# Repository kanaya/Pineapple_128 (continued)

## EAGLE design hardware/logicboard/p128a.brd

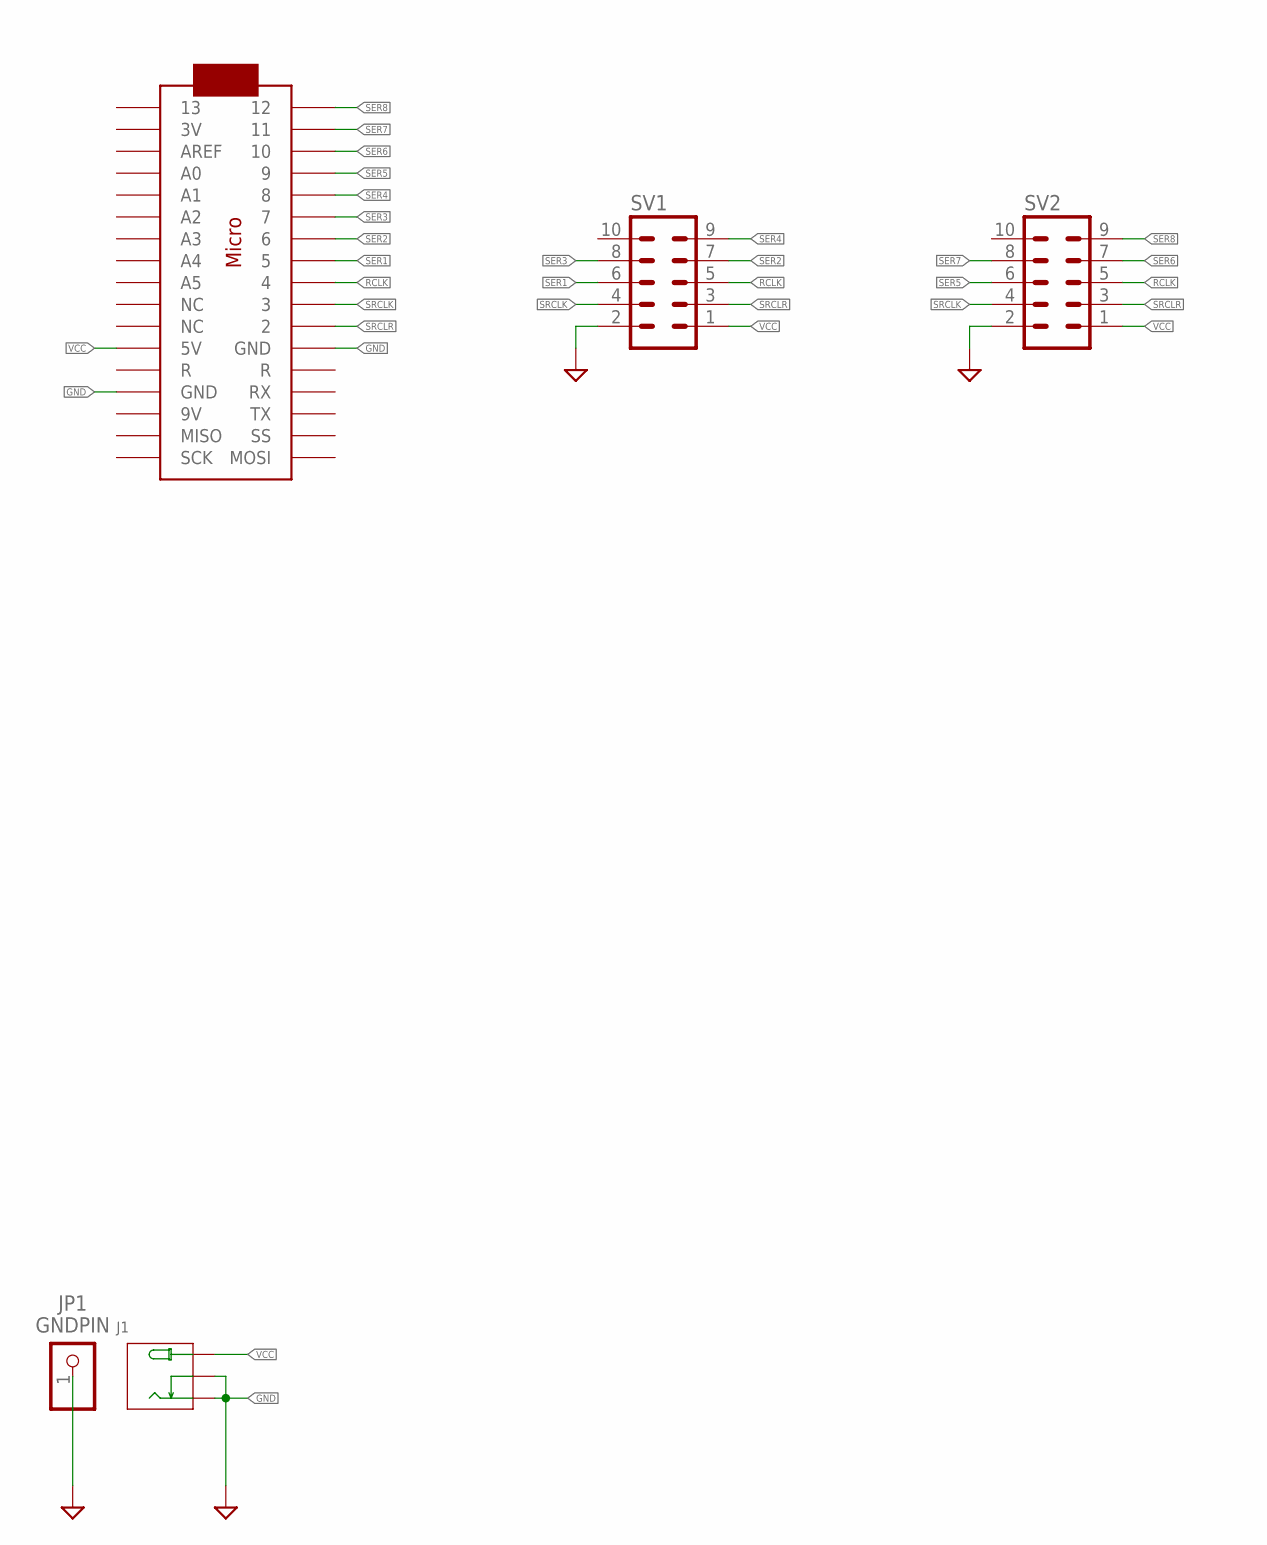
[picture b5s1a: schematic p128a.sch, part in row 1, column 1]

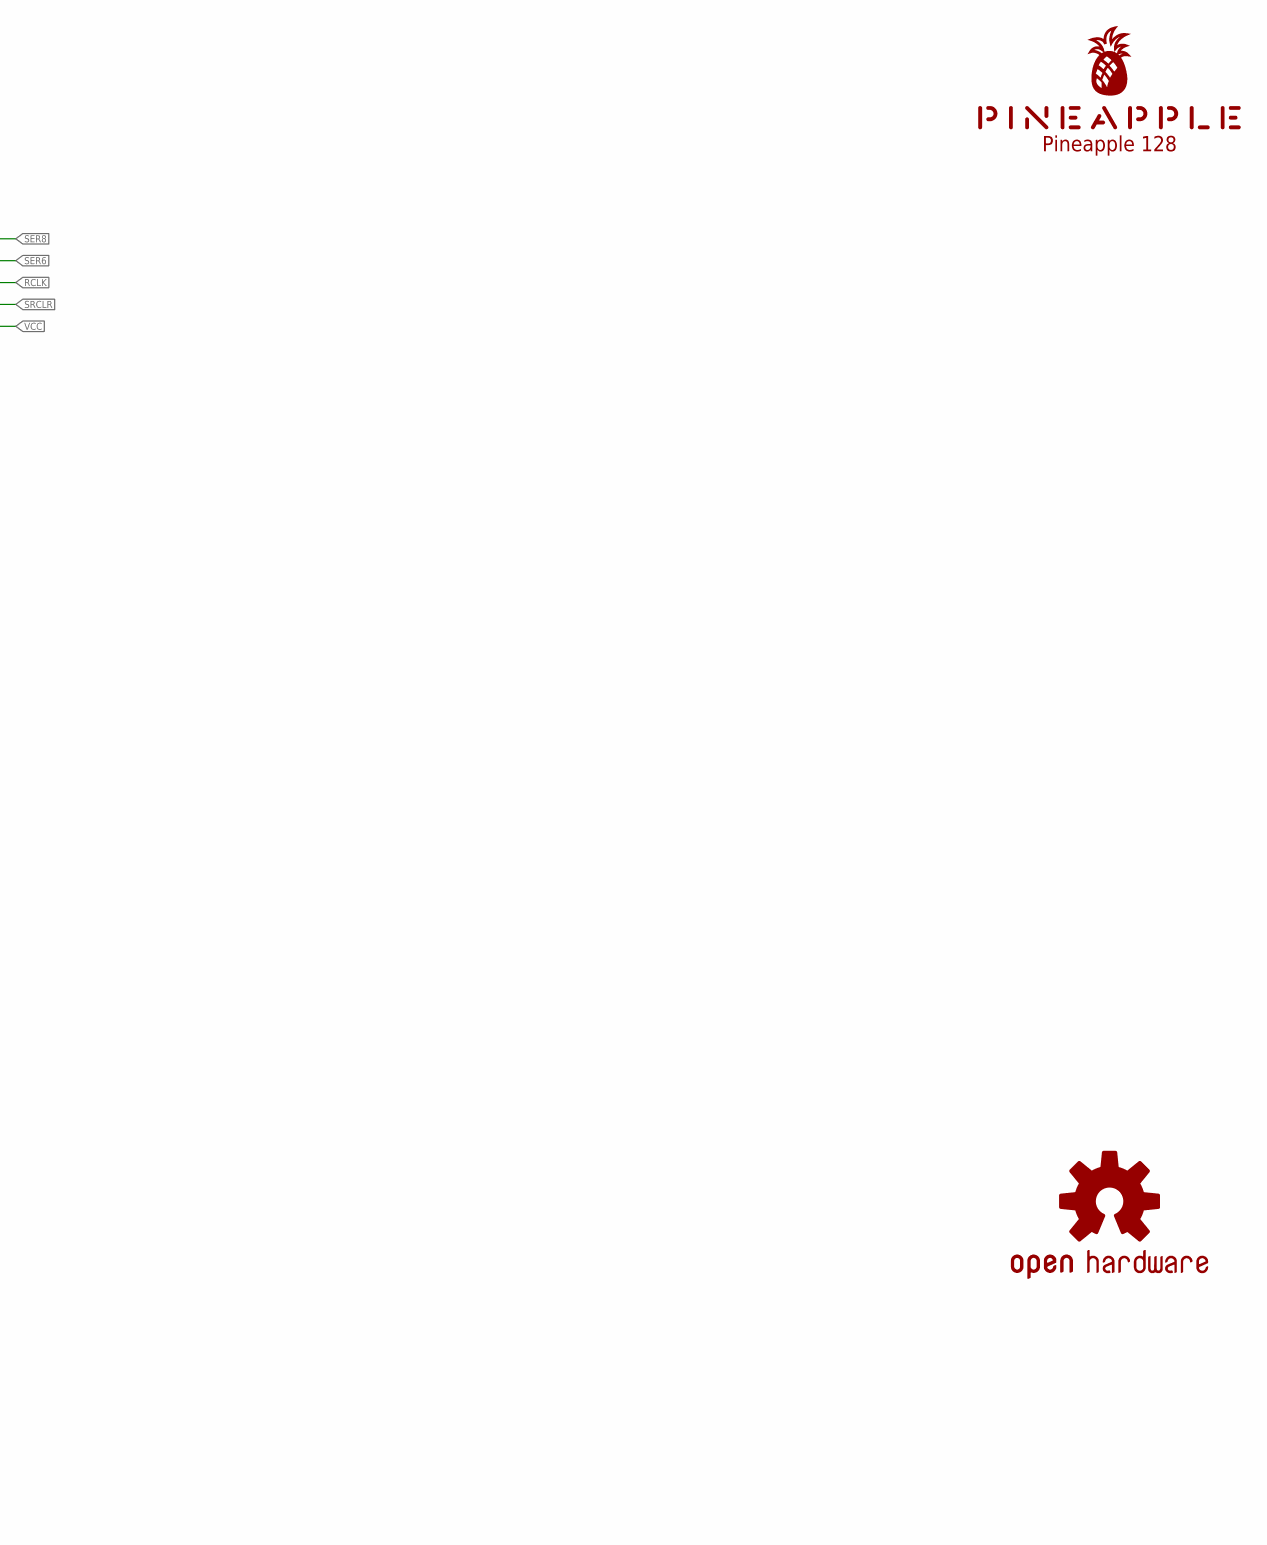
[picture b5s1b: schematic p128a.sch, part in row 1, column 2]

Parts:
J1: JACK-DC-005'DC-005'; 3P-L14.2*W11.0*H9.0MM
JP1: GNDPIN; 1X01
LOGO1: OSHW-LOGOS-COPPER; OSHW-LOGO-S_COPPER
MC1: ARDUINOMICRO
SV1, SV2: ML10L
U$1: PINEAPPLE450_SILK

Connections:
GND: J1.-1 (-), J1.-2 (CDN), JP1.1, MC1.P$12 (GND), MC1.P$21 (GND), SV1.2, SV2.2
RCLK: MC1.P$9 (4), SV1.5, SV2.5
SER1: MC1.P$8 (5), SV1.6
SER2: MC1.P$7 (6), SV1.7
SER3: MC1.P$6 (7), SV1.8
SER4: MC1.P$5 (8), SV1.9
SER5: MC1.P$4 (9), SV2.6
SER6: MC1.P$3 (10), SV2.7
SER7: MC1.P$2 (11), SV2.8
SER8: MC1.P$1 (12), SV2.9
SRCLK: MC1.P$10 (3), SV1.4, SV2.4
SRCLR: MC1.P$11 (2), SV1.3, SV2.3
VCC: J1.+, MC1.P$23 (5V), SV1.1, SV2.1

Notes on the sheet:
Pineapple 128

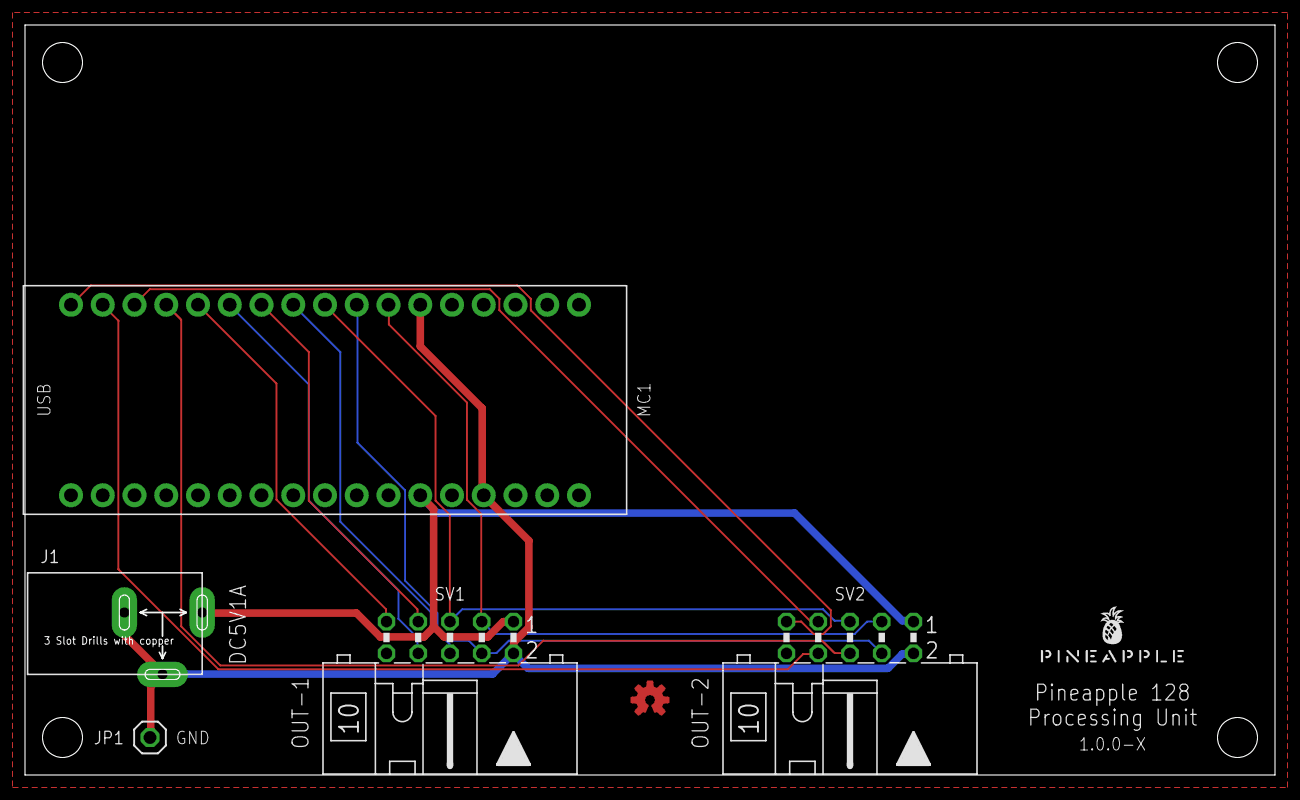
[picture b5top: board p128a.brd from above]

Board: 2 copper layers, 99.9 x 59.9 mm, 7 parts (0 on the bottom side), 13 nets.

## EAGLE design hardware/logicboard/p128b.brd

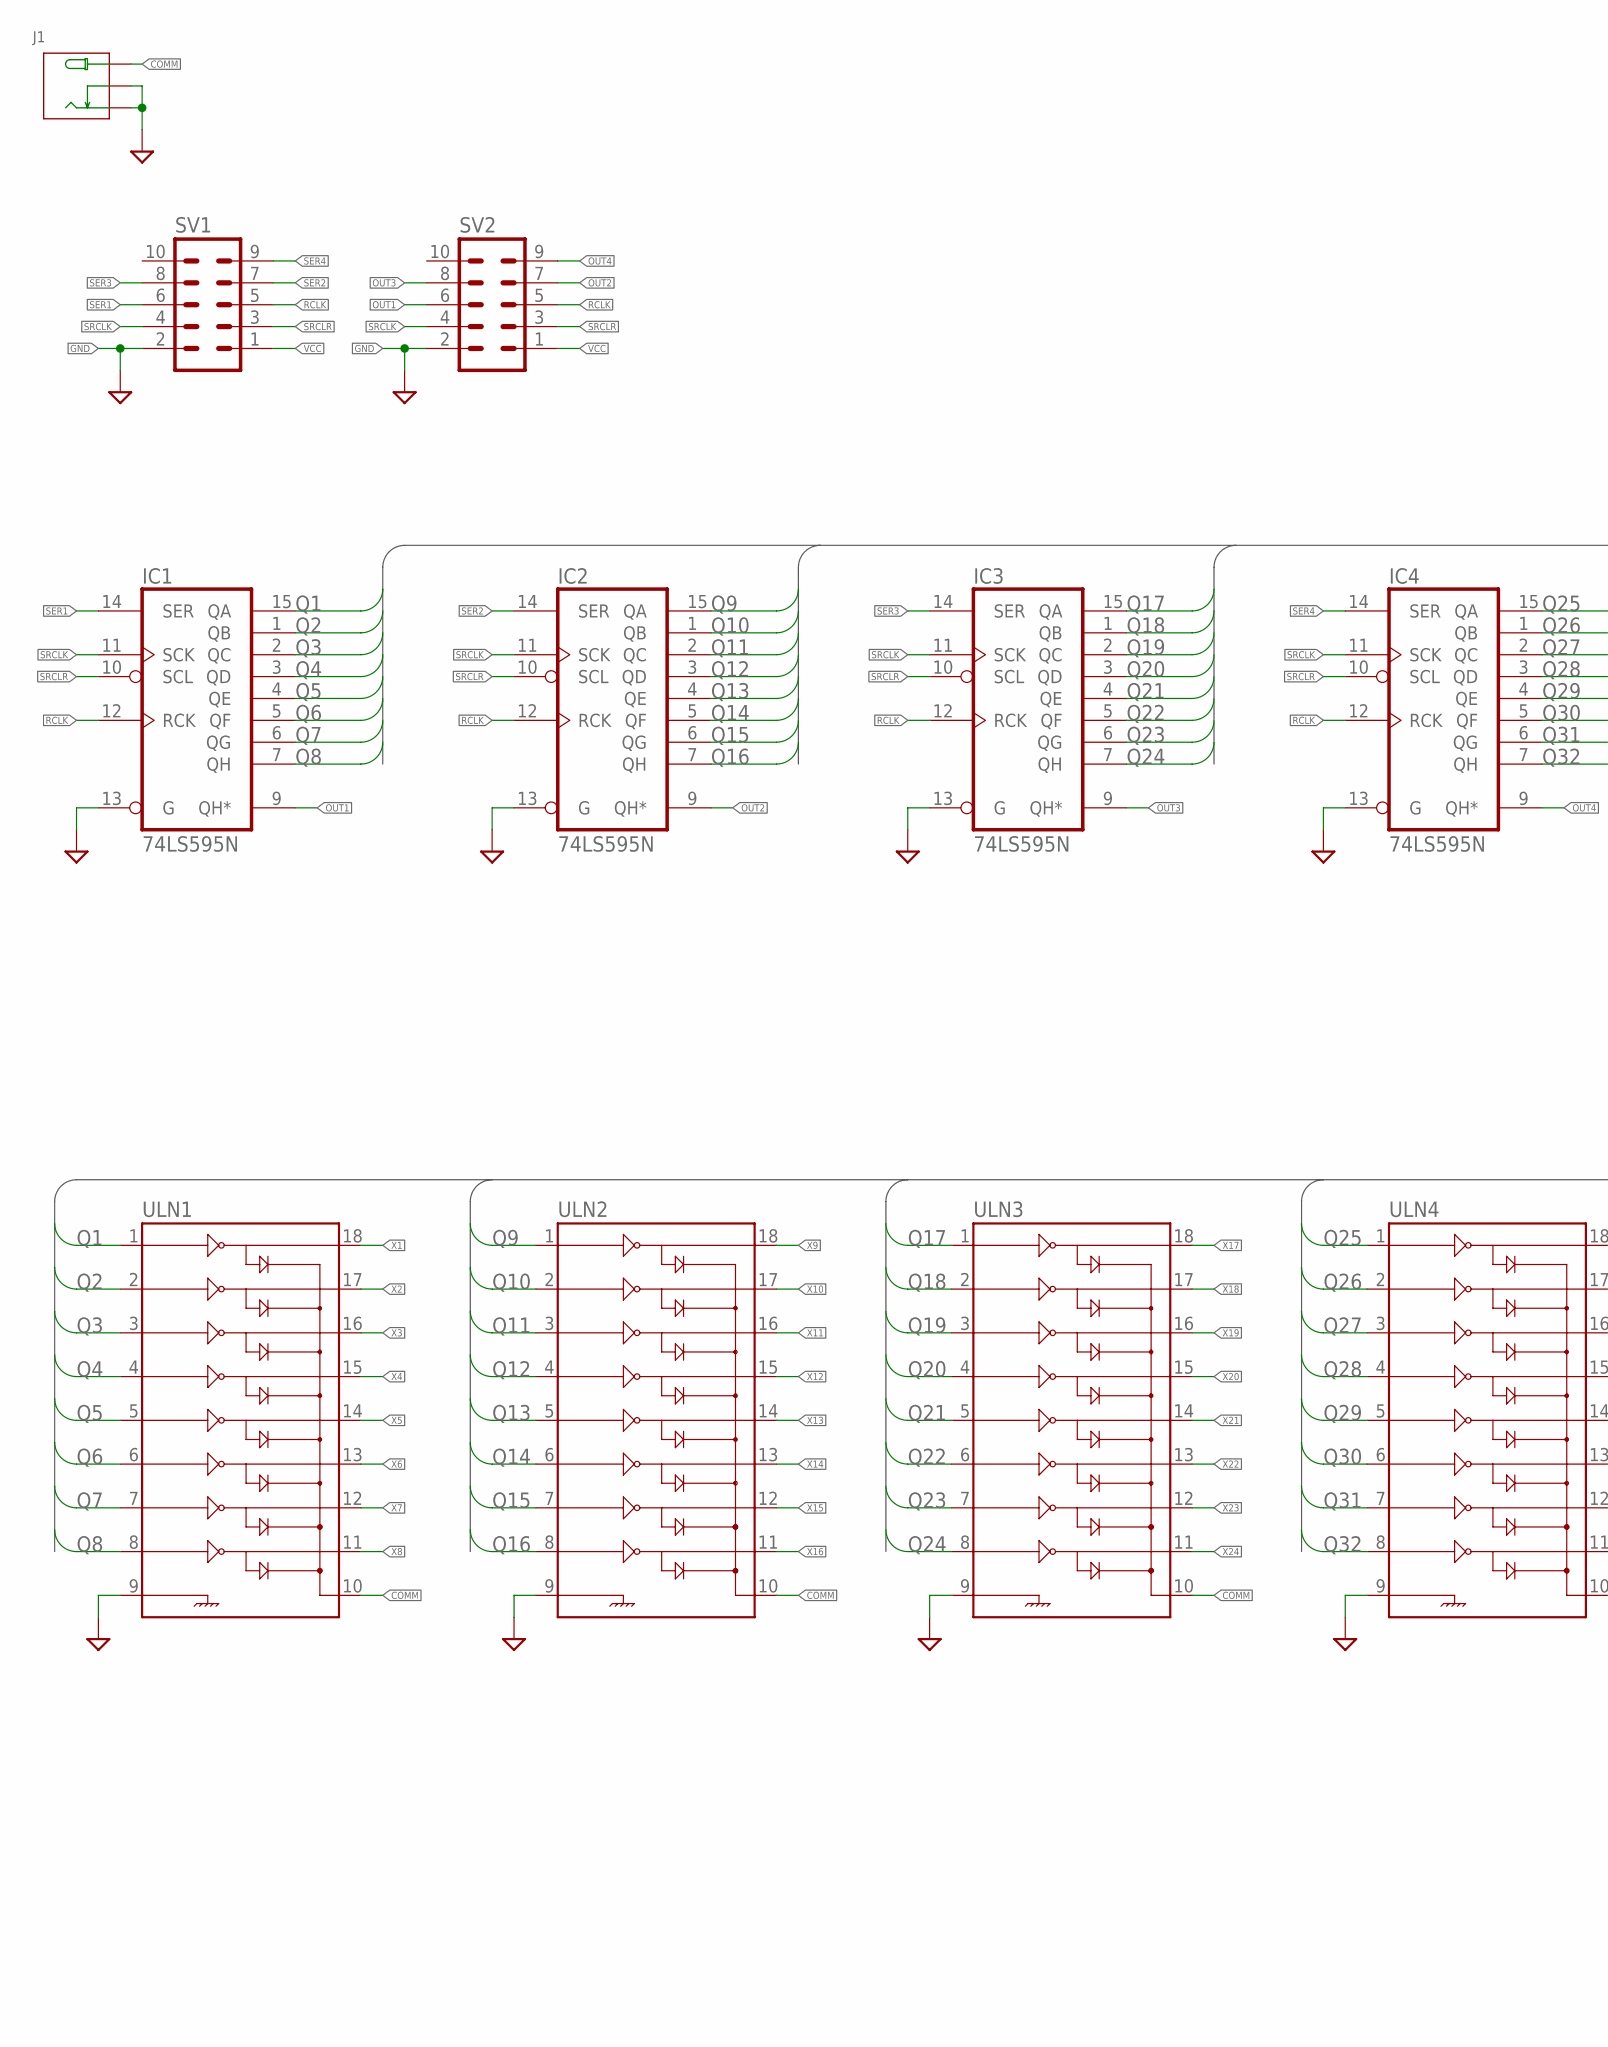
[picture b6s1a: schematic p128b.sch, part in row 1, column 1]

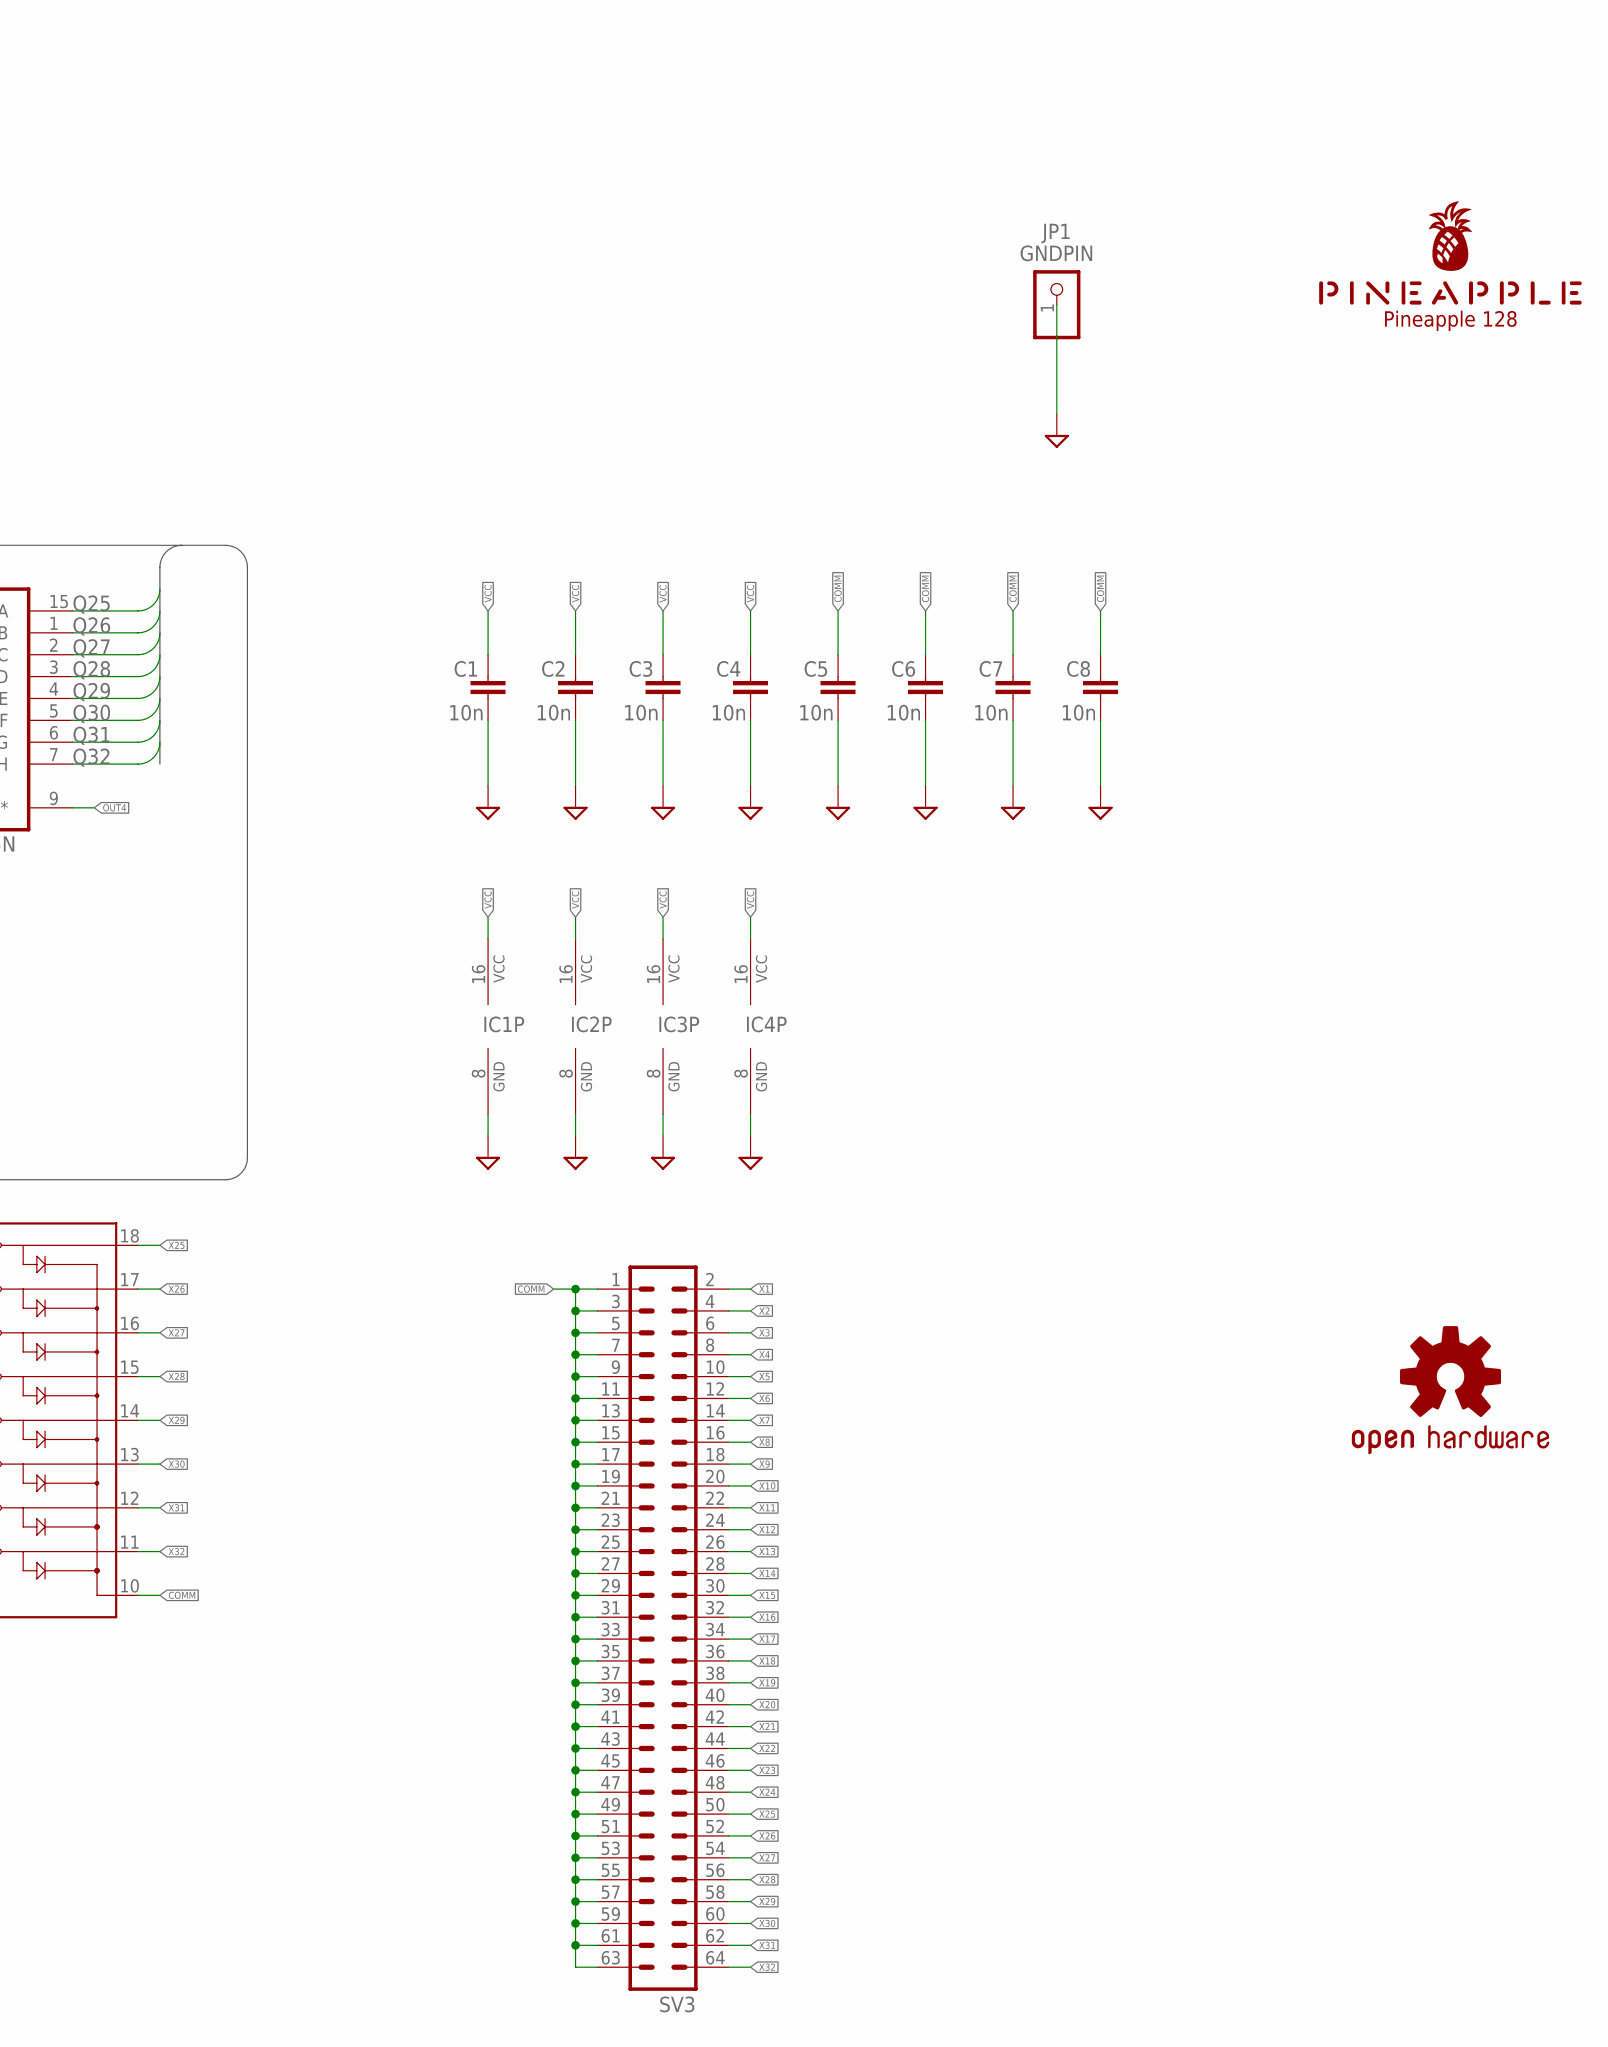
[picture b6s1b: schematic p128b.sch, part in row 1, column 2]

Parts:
C1, C2, C3, C4, C5, C6, C7, C8: 10n; C025-024X044
IC1, IC2, IC3, IC4: 74LS595N; DIL16
J1: JACK-DC-005'DC-005'; 3P-L14.2*W11.0*H9.0MM
JP1: GNDPIN; 1X01
LOGO1: OSHW-LOGOS-COPPER; OSHW-LOGO-S_COPPER
SV1, SV2: ML10L
SV3: ML64L
U$1: PINEAPPLE450_SILK
ULN1, ULN2, ULN3, ULN4: ULN2803DIP; DIL18

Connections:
COMM: C5.1, C6.1, C7.1, C8.1, J1.+, SV3.1, SV3.3, SV3.5, SV3.7, SV3.9, SV3.11, SV3.13, SV3.15, SV3.17, SV3.19, SV3.21, SV3.23, SV3.25, SV3.27, SV3.29, SV3.31, SV3.33, SV3.35, SV3.37, SV3.39, SV3.41, SV3.43, SV3.45, SV3.47, SV3.49, SV3.51, SV3.53, SV3.55, SV3.57, SV3.59, SV3.61, SV3.63, ULN1.10, ULN2.10, ULN3.10, ULN4.10
GND: C1.2, C2.2, C3.2, C4.2, C5.2, C6.2, C7.2, C8.2, IC1.8 (GND), IC1.13 (G), IC2.8 (GND), IC2.13 (G), IC3.8 (GND), IC3.13 (G), IC4.8 (GND), IC4.13 (G), J1.-1 (-), J1.-2 (CDN), JP1.1, SV1.2, SV2.2, ULN1.9, ULN2.9, ULN3.9, ULN4.9
OUT1: IC1.9 (QH*), SV2.6
OUT2: IC2.9 (QH*), SV2.7
OUT3: IC3.9 (QH*), SV2.8
OUT4: IC4.9 (QH*), SV2.9
Q1: IC1.15 (QA), ULN1.1
Q2: IC1.1 (QB), ULN1.2
Q3: IC1.2 (QC), ULN1.3
Q4: IC1.3 (QD), ULN1.4
Q5: IC1.4 (QE), ULN1.5
Q6: IC1.5 (QF), ULN1.6
Q7: IC1.6 (QG), ULN1.7
Q8: IC1.7 (QH), ULN1.8
Q9: IC2.15 (QA), ULN2.1
Q10: IC2.1 (QB), ULN2.2
Q11: IC2.2 (QC), ULN2.3
Q12: IC2.3 (QD), ULN2.4
Q13: IC2.4 (QE), ULN2.5
Q14: IC2.5 (QF), ULN2.6
Q15: IC2.6 (QG), ULN2.7
Q16: IC2.7 (QH), ULN2.8
Q17: IC3.15 (QA), ULN3.1
Q18: IC3.1 (QB), ULN3.2
Q19: IC3.2 (QC), ULN3.3
Q20: IC3.3 (QD), ULN3.4
Q21: IC3.4 (QE), ULN3.5
Q22: IC3.5 (QF), ULN3.6
Q23: IC3.6 (QG), ULN3.7
Q24: IC3.7 (QH), ULN3.8
Q25: IC4.15 (QA), ULN4.1
Q26: IC4.1 (QB), ULN4.2
Q27: IC4.2 (QC), ULN4.3
Q28: IC4.3 (QD), ULN4.4
Q29: IC4.4 (QE), ULN4.5
Q30: IC4.5 (QF), ULN4.6
Q31: IC4.6 (QG), ULN4.7
Q32: IC4.7 (QH), ULN4.8
RCLK: IC1.12 (RCK), IC2.12 (RCK), IC3.12 (RCK), IC4.12 (RCK), SV1.5, SV2.5
SER1: IC1.14 (SER), SV1.6
SER2: IC2.14 (SER), SV1.7
SER3: IC3.14 (SER), SV1.8
SER4: IC4.14 (SER), SV1.9
SRCLK: IC1.11 (SCK), IC2.11 (SCK), IC3.11 (SCK), IC4.11 (SCK), SV1.4, SV2.4
SRCLR: IC1.10 (SCL), IC2.10 (SCL), IC3.10 (SCL), IC4.10 (SCL), SV1.3, SV2.3
VCC: C1.1, C2.1, C3.1, C4.1, IC1.16 (VCC), IC2.16 (VCC), IC3.16 (VCC), IC4.16 (VCC), SV1.1, SV2.1
X1: SV3.2, ULN1.18
X2: SV3.4, ULN1.17
X3: SV3.6, ULN1.16
X4: SV3.8, ULN1.15
X5: SV3.10, ULN1.14
X6: SV3.12, ULN1.13
X7: SV3.14, ULN1.12
X8: SV3.16, ULN1.11
X9: SV3.18, ULN2.18
X10: SV3.20, ULN2.17
X11: SV3.22, ULN2.16
X12: SV3.24, ULN2.15
X13: SV3.26, ULN2.14
X14: SV3.28, ULN2.13
X15: SV3.30, ULN2.12
X16: SV3.32, ULN2.11
X17: SV3.34, ULN3.18
X18: SV3.36, ULN3.17
X19: SV3.38, ULN3.16
X20: SV3.40, ULN3.15
X21: SV3.42, ULN3.14
X22: SV3.44, ULN3.13
X23: SV3.46, ULN3.12
X24: SV3.48, ULN3.11
X25: SV3.50, ULN4.18
X26: SV3.52, ULN4.17
X27: SV3.54, ULN4.16
X28: SV3.56, ULN4.15
X29: SV3.58, ULN4.14
X30: SV3.60, ULN4.13
X31: SV3.62, ULN4.12
X32: SV3.64, ULN4.11

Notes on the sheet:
Pineapple 128

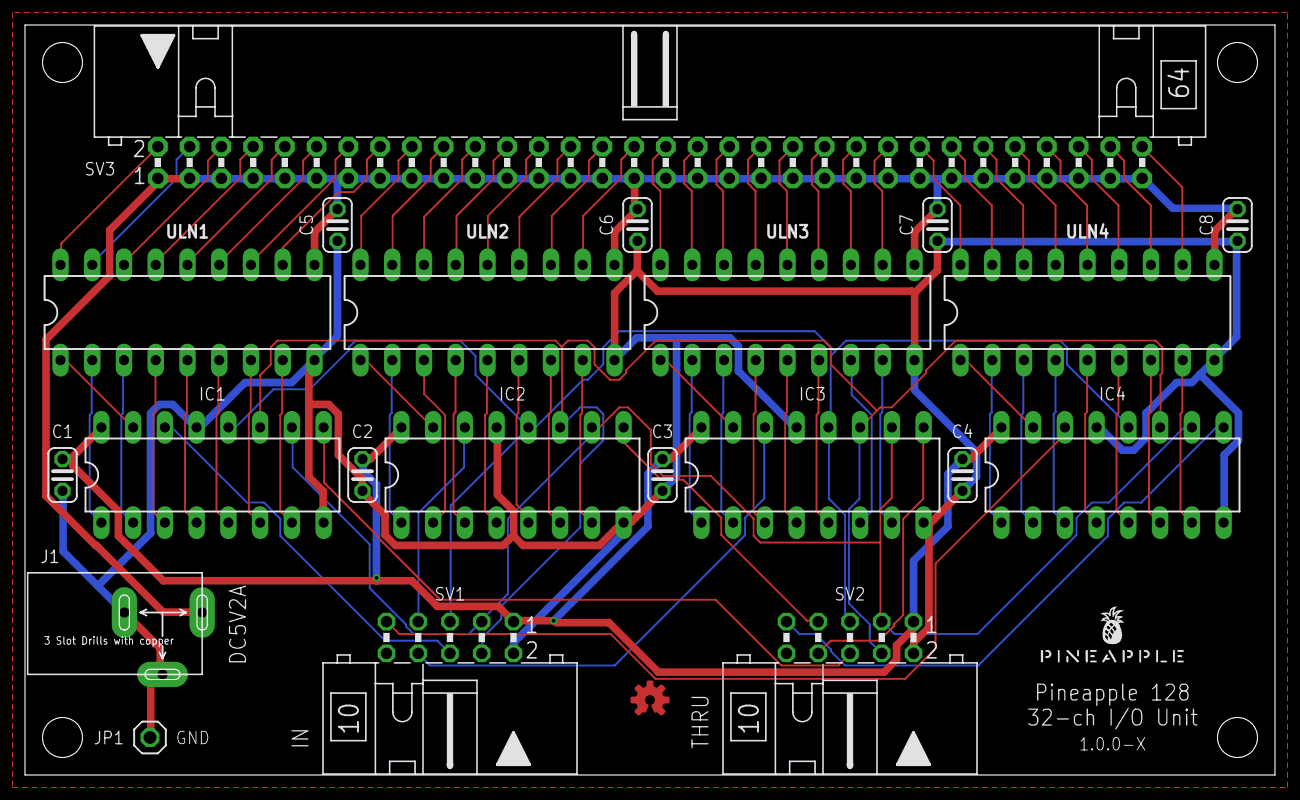
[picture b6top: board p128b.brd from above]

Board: 2 copper layers, 99.9 x 59.9 mm, 23 parts (0 on the bottom side), 78 nets.

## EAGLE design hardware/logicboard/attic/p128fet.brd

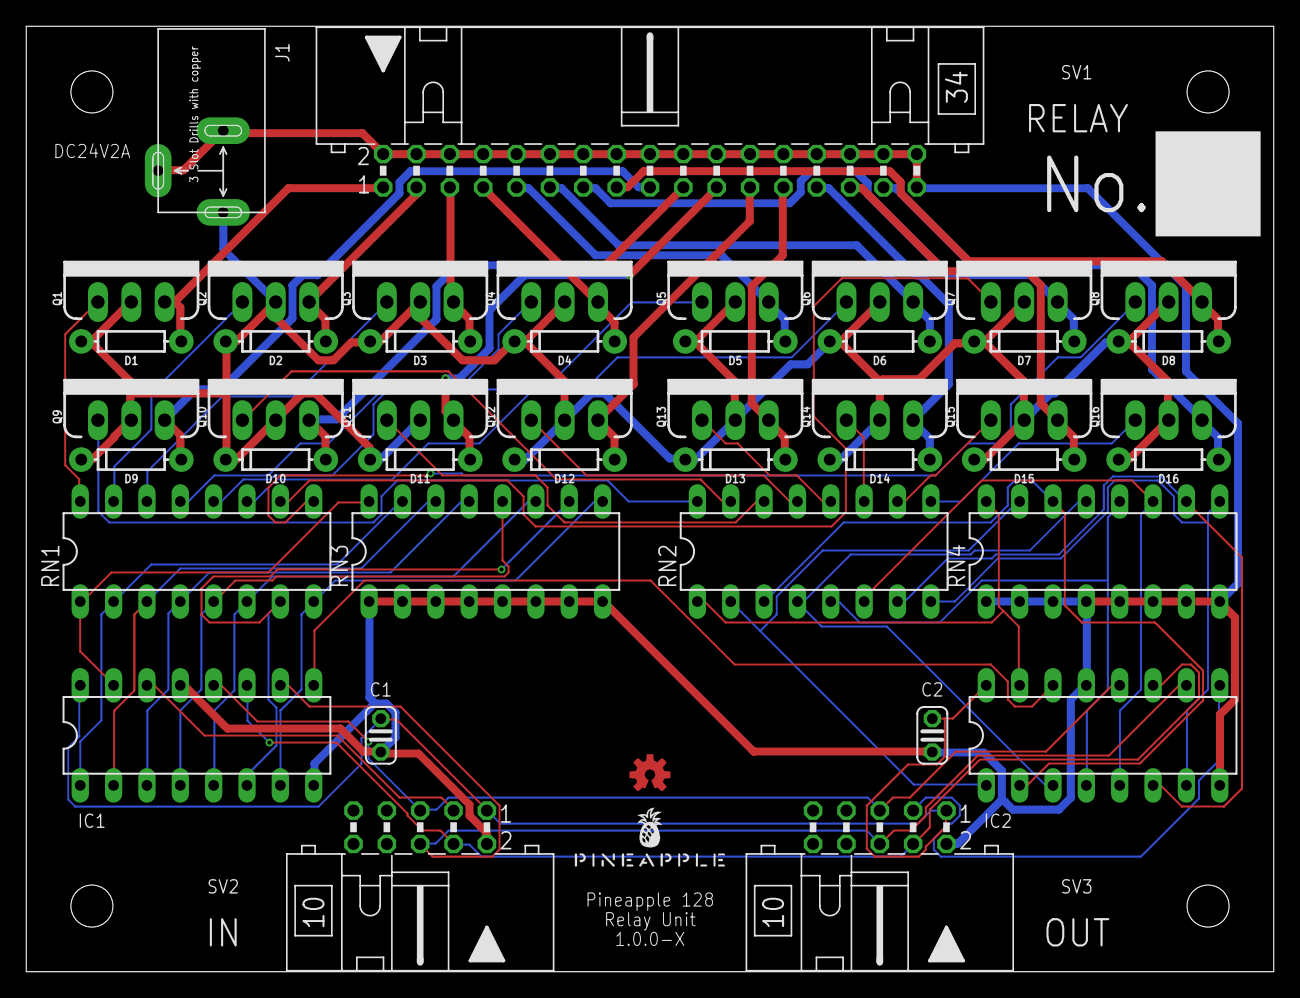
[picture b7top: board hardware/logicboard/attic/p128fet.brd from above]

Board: 2 copper layers, 94.9 x 71.9 mm, 46 parts (0 on the bottom side), 57 nets.

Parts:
C1, C2: C025-024X044
D1, D2, D3, D4, D5, D6, D7, D8, D9, D10, D11, D12, D13, D14, D15, D16: 200mA/100V/1V; DIODE-1N4148
IC1, IC2: 74LS595N; DIL16
J1: 3P-L14.2*W11.0*H9.0MM
LOGO1: OSHW-LOGOS-COPPER; OSHW-LOGO-S_COPPER
Q1, Q2, Q3, Q4, Q5, Q6, Q7, Q8, Q9, Q10, Q11, Q12, Q13, Q14, Q15, Q16: 60V/32A/35mΩ; TO220V
RN1, RN2: 220; DIL16
RN3, RN4: 10k; DIL16
SV1: ML34L
SV2, SV3: ML10L
U$1: PINEAPPLE450_SILK

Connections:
+24V: D1.C, D2.C, D3.C, D4.C, D5.C, D6.C, D7.C, D8.C, D9.C, D10.C, D11.C, D12.C, D13.C, D14.C, D15.C, D16.C, J1.+, Q1.2, Q2.2, Q3.2, Q4.2, Q5.2, Q6.2, Q7.2, Q8.2, Q9.2, Q10.2, Q11.2, Q12.2, Q13.2, Q14.2, Q15.2, Q16.2
CLR: IC1.10, IC2.10, SV2.6, SV3.6
GND: C1.2, C2.2, IC1.8, IC1.13, IC2.8, IC2.13, J1.-1, J1.-2, RN3.1, RN3.2, RN3.3, RN3.4, RN3.5, RN3.6, RN3.7, RN3.8, RN4.1, RN4.2, RN4.3, RN4.4, RN4.5, RN4.6, RN4.7, RN4.8, SV1.2, SV1.4, SV1.6, SV1.8, SV1.10, SV1.12, SV1.14, SV1.16, SV1.18, SV1.20, SV1.22, SV1.24, SV1.26, SV1.28, SV1.30, SV1.32, SV1.33, SV1.34, SV2.2, SV3.2
unnamed: Q1.1, RN1.16
unnamed: Q2.1, RN1.15
unnamed: Q3.1, RN1.14
unnamed: Q4.1, RN1.13
unnamed: Q5.1, RN1.12
unnamed: Q6.1, RN1.11
unnamed: Q7.1, RN1.10
unnamed: Q8.1, RN1.9
unnamed: IC1.9, IC2.14
unnamed: Q9.1, RN2.16
unnamed: Q10.1, RN2.15
unnamed: Q14.1, RN2.11
unnamed: Q11.1, RN2.14
unnamed: Q15.1, RN2.10
unnamed: Q12.1, RN2.13
unnamed: Q16.1, RN2.9
unnamed: Q13.1, RN2.12
RCLK: IC1.12, IC2.12, SV2.5, SV3.5
S1: IC1.15, RN1.1, RN3.16
S2: IC1.1, RN1.2, RN3.15
S3: IC1.2, RN1.3, RN3.14
S4: IC1.3, RN1.4, RN3.13
S5: IC1.4, RN1.5, RN3.12
S6: IC1.5, RN1.6, RN3.11
S7: IC1.6, RN1.7, RN3.10
S8: IC1.7, RN1.8, RN3.9
S9: IC2.15, RN2.1, RN4.16
S10: IC2.1, RN2.2, RN4.15
S11: IC2.2, RN2.3, RN4.14
S12: IC2.3, RN2.4, RN4.13
S13: IC2.4, RN2.5, RN4.12
S14: IC2.5, RN2.6, RN4.11
S15: IC2.6, RN2.7, RN4.10
S16: IC2.7, RN2.8, RN4.9
SCLK: IC1.11, IC2.11, SV2.4, SV3.4
SIN: IC1.14, SV2.3
SOUT: IC2.9, SV3.3
VCC: C1.1, C2.1, IC1.16, IC2.16, SV2.1, SV3.1
X1: D1.A, Q1.3, SV1.1
X2: D2.A, Q2.3, SV1.3
X3: D3.A, Q3.3, SV1.5
X4: D4.A, Q4.3, SV1.7
X5: D5.A, Q5.3, SV1.9
X6: D6.A, Q6.3, SV1.11
X7: D7.A, Q7.3, SV1.13
X8: D8.A, Q8.3, SV1.15
X9: D9.A, Q9.3, SV1.17
X10: D10.A, Q10.3, SV1.19
X11: D11.A, Q11.3, SV1.21
X12: D12.A, Q12.3, SV1.23
X13: D13.A, Q13.3, SV1.25
X14: D14.A, Q14.3, SV1.27
X15: D15.A, Q15.3, SV1.29
X16: D16.A, Q16.3, SV1.31

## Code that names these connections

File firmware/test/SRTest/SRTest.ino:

const int A         =  200;  // ONタイム  [msec]
const int B         =  200;  // OFFタイム [msec]
const int C         =  20;   // 1chずつずらすタイミング [msec] （0の場合は全チャンネル一斉にオンオフする）

const int N         =  8;    // 電磁弁の数

const int PIN_CLR   =  2;
const int PIN_SCLK  =  3;
const int PIN_RCLK  =  4;
const int PIN_SOUT1 =  5;

void full_reset() {
  digitalWrite(PIN_CLR, LOW);
  delay(10);
  digitalWrite(PIN_CLR, HIGH);
}

void setup() {
  pinMode(PIN_SOUT1, OUTPUT);
  pinMode(PIN_RCLK,  OUTPUT);
  pinMode(PIN_SCLK,  OUTPUT);
  pinMode(PIN_CLR,   OUTPUT);

  digitalWrite(PIN_CLR, HIGH);
}

void loop() { 
  if (C == 0) {
    // 全チャンネル同時にオンオフする
    // ON
    digitalWrite(PIN_RCLK, LOW);
    shiftOut(PIN_SOUT1, PIN_SCLK, LSBFIRST, B11111111);
    digitalWrite(PIN_RCLK, HIGH);
    delay(A);
    // OFF
    digitalWrite(PIN_RCLK, LOW);
    shiftOut(PIN_SOUT1, PIN_SCLK, LSBFIRST, B00000000);
    digitalWrite(PIN_RCLK, HIGH);
    delay(B);
  }
  else {
    // 1chずつずらしてオンオフする
    if (C * N < A) {
      // C * N << A の場合
      // ON
      int bitPattern = B00000001;
      for (int i = 0; i < N; ++i) {
        digitalWrite(PIN_RCLK, LOW);
        shiftOut(PIN_SOUT1, PIN_SCLK, LSBFIRST, bitPattern);
        digitalWrite(PIN_RCLK, HIGH);
        bitPattern <<= 1;
        bitPattern |= 1;
        delay(C);
      }
      delay(A);
      // OFF
      bitPattern = B11111110;
      for (int i = 0; i < N; ++i) {
        digitalWrite(PIN_RCLK, LOW);
        shiftOut(PIN_SOUT1, PIN_SCLK, LSBFIRST, bitPattern);
        digitalWrite(PIN_RCLK, HIGH);
        bitPattern <<= 1;
        delay(C);
      }
      delay(B);
    }
    else {
      // C * N >> A + B の場合
      int bitPattern = B00000001;
      for (int i = 0; i < N; ++i) {
        // ON
        digitalWrite(PIN_RCLK, LOW);
        shiftOut(PIN_SOUT1, PIN_SCLK, LSBFIRST, bitPattern);
        digitalWrite(PIN_RCLK, HIGH);
        bitPattern <<= 1;
        delay(A);
        // OFF
        digitalWrite(PIN_RCLK, LOW);
        shiftOut(PIN_SOUT1, PIN_SCLK, LSBFIRST, B00000000);
        digitalWrite(PIN_RCLK, HIGH);
        delay(B);
      }
      delay(C);
    }
  }
}

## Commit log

2020-06-08 Initial commit. Copied from Pineapple II 0cf6762ab812fbb6074f1b51056c38a608ab3501.
2020-06-08 First try.
2020-06-08 Added gitignore.
2020-06-08 Changing PCB size.
2020-06-08 Packing in 80x80mm...
2020-06-09 Separated into 2 boards.
2020-06-09 Silk.
2020-06-09 Unified A-board and B-board.
2020-06-09 Removed A-board and B-board.
2020-06-11 Designing Relay board.
2020-06-11 Added Processing Unit.
2020-06-11 Removed unused files.
2020-06-12 Added MIDI-IN.
2020-06-12 Re-designed the controller.
2020-06-12 Release candidate.
2020-06-13 Removed old file.
2020-06-17 Imported Blink sketch.
2020-06-17 First working version.
2020-06-17 Knight rider mode.
2020-06-17 Added "how to connect" image.
2020-06-19 Communication in ASCII mode.
2020-06-19 Binary communication.
2020-06-22 Started design of FET version.
2020-06-22 Added FET version.
2020-06-23 Added necontrol and necodrive.
2020-06-23 Nocontrol 128-ch out.
2020-06-23 First working necontrol.
2020-06-23 Compiled Necontrol.
2020-06-23 Now necontroler (Necobit Controler) has LED indicator.
2020-06-23 Removed gerber files.
2020-06-23 Moved the original control to attic.
2020-06-23 Removed necodrive.
2020-06-23 Moved FET drive to attic.
2020-06-23 Moved relay board to attic.
2020-06-23 Rename.
2020-06-23 Fine tuning.
2020-06-23 More fine tune.
2020-06-23 Fine fine tuning.
